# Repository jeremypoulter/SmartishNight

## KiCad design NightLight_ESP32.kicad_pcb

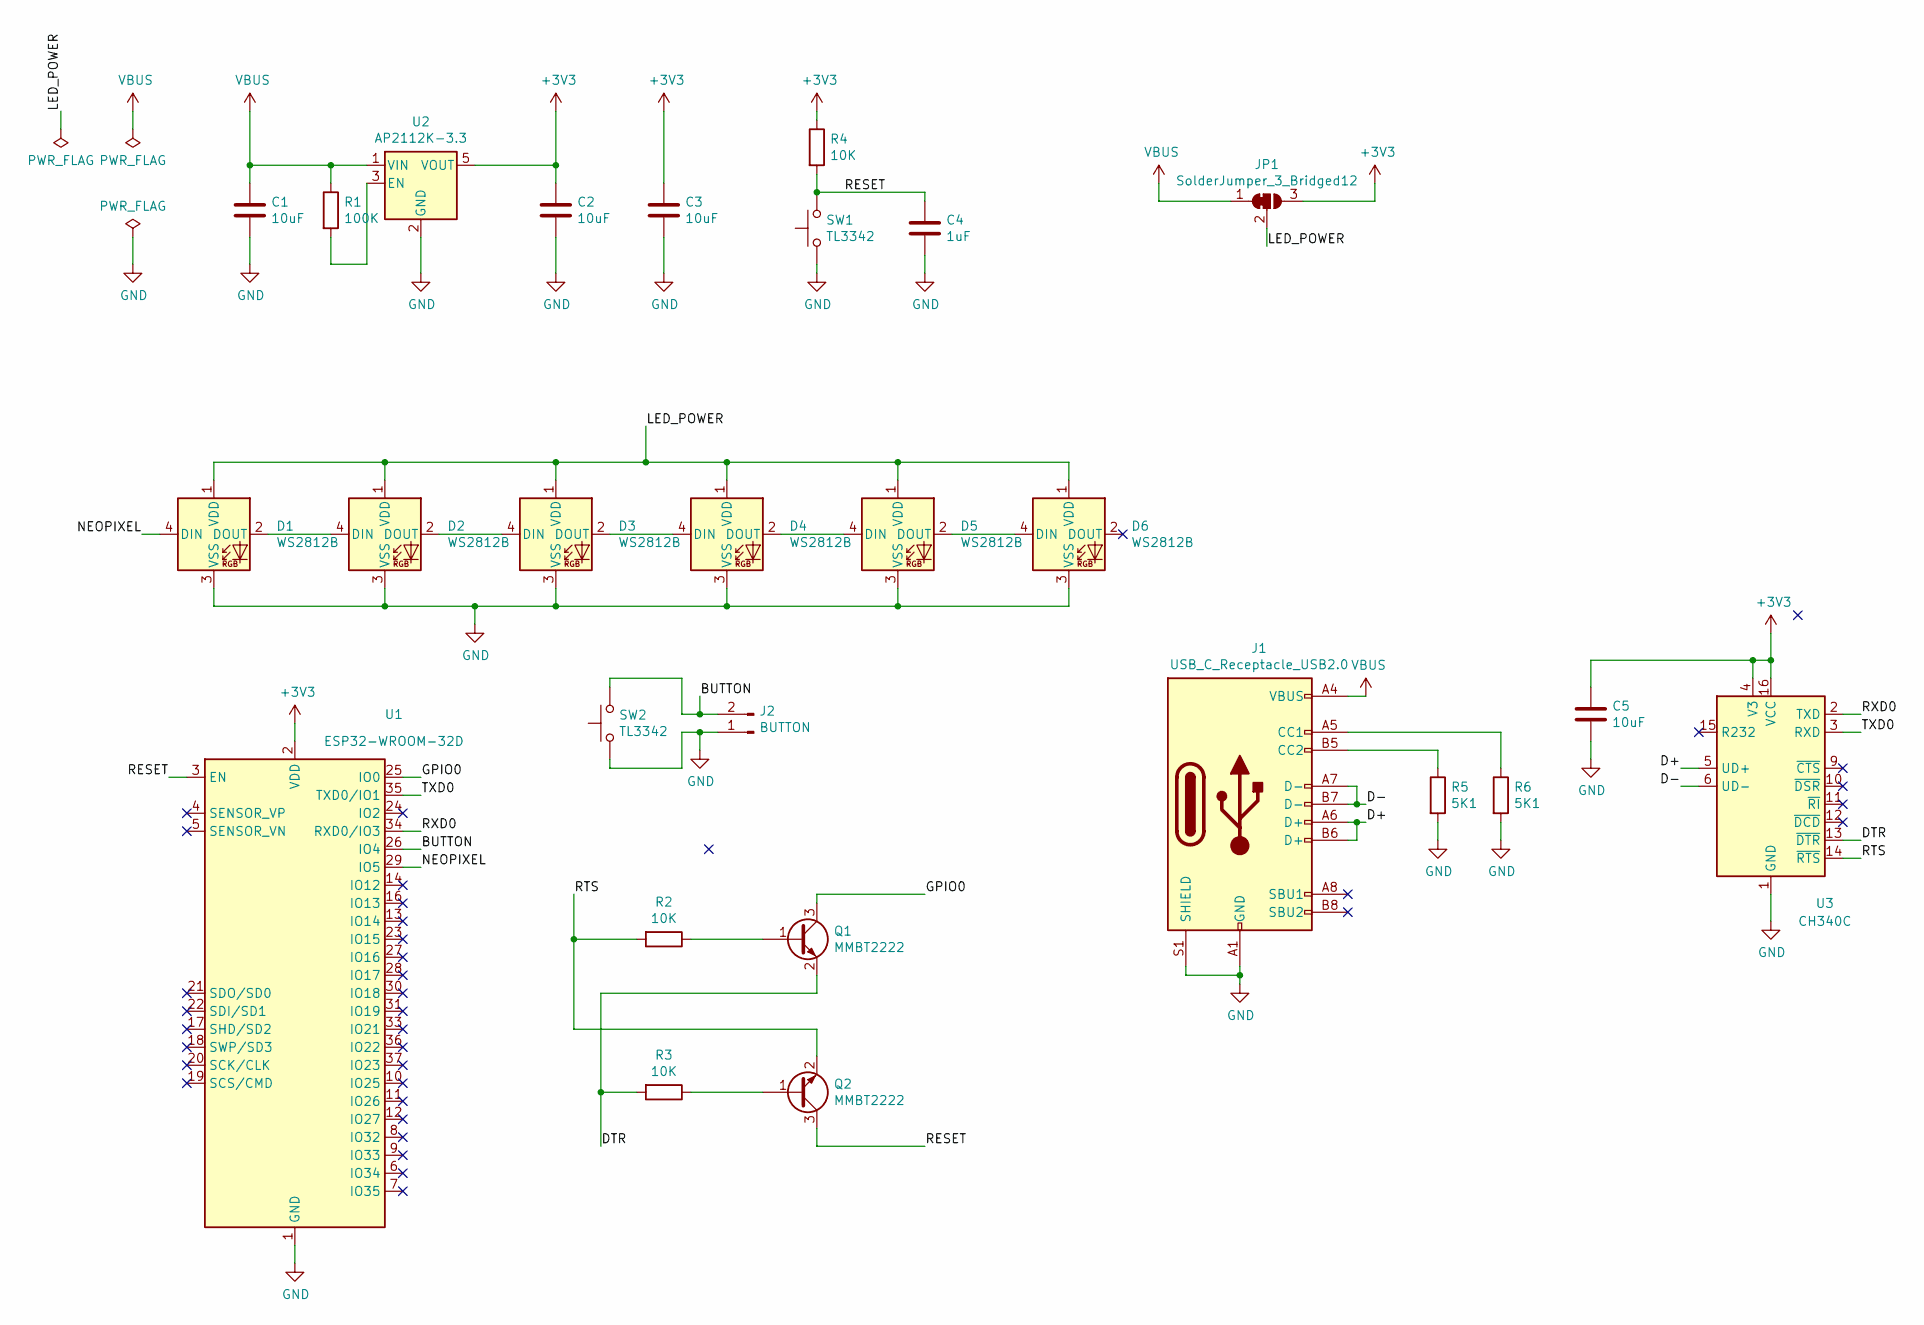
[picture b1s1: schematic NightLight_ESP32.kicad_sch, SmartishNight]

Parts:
C1, C2, C3, C5: 10uF; C_0805_2012Metric; LCSC C15850
C4: 1uF; C_0805_2012Metric; LCSC C28323
D1: WS2812B; LED_WS2812B_PLCC4_5.0x5.0mm_P3.2mm; LCSC C114586
D2, D3, D4, D5, D6: WS2812B; LED_WS2812B_PLCC4_5.0x5.0mm_P3.2mm; JLCPCB_CORRECTION 0;0;180
J1: USB_C_Receptacle_USB2.0; USB_C_Receptacle_HRO_TYPE-C-31-M-12; LCSC C165948
J2: BUTTON; PinHeader_1x02_P2.54mm_Vertical
JP1: SolderJumper_3_Bridged12; SolderJumper-3_P1.3mm_Bridged12_RoundedPad1.0x1.5mm
Q1, Q2: MMBT2222; SOT-23
R1: 100K; R_0805_2012Metric; LCSC C17407
R2, R3, R4: 10K; R_0805_2012Metric; LCSC C17414
R5, R6: 5K1; R_0805_2012Metric; LCSC C27834
SW1, SW2: TL3342; SW_SPST_TL3342; LCSC C318884
U1: ESP32-WROOM-32D; ESP32-WROOM-32; LCSC C473012
U2: AP2112K-3.3; SOT-23-5; LCSC C51118
U3: CH340C; SOIC-16_3.9x9.9mm_P1.27mm; LCSC C84681

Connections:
+3V3: C2.1, C3.1, C5.1, JP1.3 (B), R4.1, U1.2 (VDD), U2.5 (VOUT), U3.4 (V3), U3.16 (VCC)
/BUTTON: J2.2, SW2.2, U1.26 (IO4)
/D+: J1.A6 (D+), J1.B6 (D+), U3.5 (UD+)
/D-: J1.A7 (D-), J1.B7 (D-), U3.6 (UD-)
/DTR: Q1.2 (E), R3.2, U3.13 (~DTR)
/GPIO0: Q1.3 (C), U1.25 (IO0)
/LED_POWER: D1.1 (VDD), D2.1 (VDD), D3.1 (VDD), D4.1 (VDD), D5.1 (VDD), D6.1 (VDD), JP1.2 (C)
/NEOPIXEL: D1.4 (DIN), U1.29 (IO5)
/RESET: C4.2, Q2.3 (C), R4.2, SW1.2, U1.3 (EN)
/RTS: Q2.2 (E), R2.2, U3.14 (~RTS)
/RXD0: U1.34 (RXD0/IO3), U3.2 (TXD)
/TXD0: U1.35 (TXD0/IO1), U3.3 (RXD)
GND: C1.2, C2.2, C3.2, C4.1, C5.2, D1.3 (VSS), D2.3 (VSS), D3.3 (VSS), D4.3 (VSS), D5.3 (VSS), D6.3 (VSS), J1.A1 (GND), J1.A12 (GND), J1.B1 (GND), J1.B12 (GND), J1.S1 (SHIELD), J2.1, R5.2, R6.2, SW1.1, SW2.1, U1.1 (GND), U1.15 (GND), U1.38 (GND), U1.39 (GND), U2.2 (GND), U3.1 (GND)
unnamed: D1.2 (DOUT), D2.4 (DIN)
unnamed: D2.2 (DOUT), D3.4 (DIN)
unnamed: D3.2 (DOUT), D4.4 (DIN)
unnamed: D4.2 (DOUT), D5.4 (DIN)
unnamed: D5.2 (DOUT), D6.4 (DIN)
unnamed: J1.A5 (CC1), R6.1
unnamed: J1.B5 (CC2), R5.1
unnamed: Q1.1 (B), R2.1
unnamed: Q2.1 (B), R3.1
unnamed: R1.2, U2.3 (EN)
VBUS: C1.1, J1.A4 (VBUS), J1.A9 (VBUS), J1.B4 (VBUS), J1.B9 (VBUS), JP1.1 (A), R1.1, U2.1 (VIN)

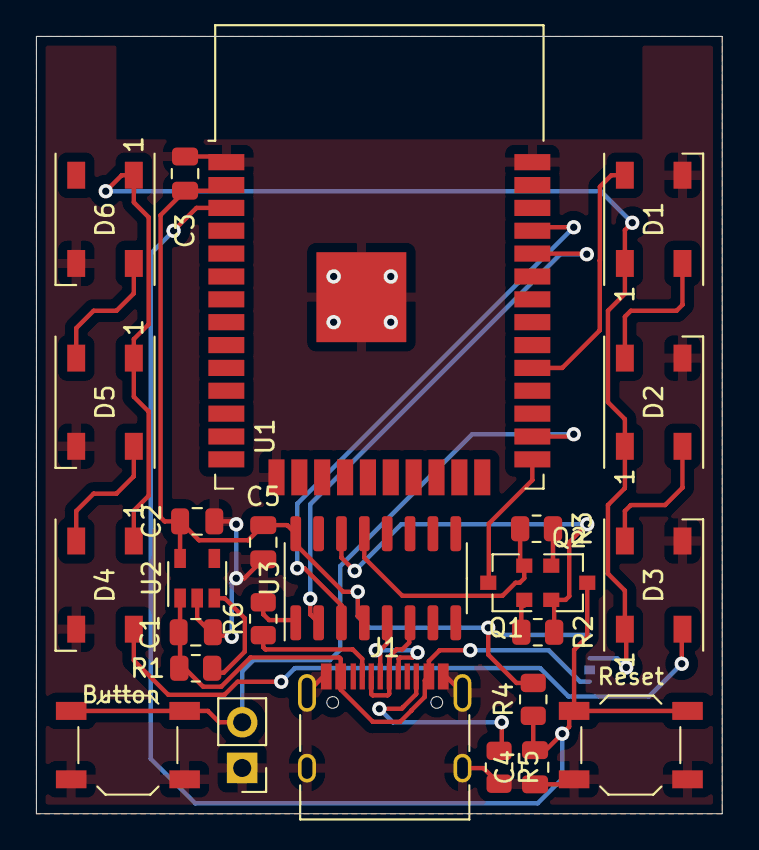
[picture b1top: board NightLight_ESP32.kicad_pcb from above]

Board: 2 copper layers, 38.1 x 43.2 mm, 27 parts (1 on the bottom side), 24 nets.

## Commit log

2020-11-03 Initial version
2020-11-03 Testing workflows for KiCAD
2020-11-03 Fixed spacing
2020-11-03 Updated sheet info
2020-11-03 Fix workflows
2020-11-03 Test commit
2020-11-03 Fixed name
2020-11-03 Fixed unconnected fills
2020-11-03 Tidy up of the silk screen
2020-11-03 Removed, not needed
2020-11-03 Adding fabrications job
2020-11-03 Renamed
2020-11-03 Trigger action
2020-11-03 Fixed unconnected GND area
2020-12-30 Fixed issues with serial lines not being connected correctly
2021-02-11 Updated LEDs power to be configurable from 5V or 3.3V
    Should be ok with a small circuot like this but close to the limits
2021-02-11 Fixed unconneced gnounds and a few other bits of tidy up
2021-02-11 Updated kicad-exports and generate JLCPCB BOM and position files
2021-02-11 Adding the workflow to the list of paths that will trigger the workflow
2021-02-11 Fix for action error
2021-02-11 Another attempt to run action on change to workflow
2021-02-11 Corrected kicad-exports version number
2021-02-11 The kicad-exports does not include the JLCPCB files, so adding locally
2021-02-11 Include JLCPCB files in workflow
2021-04-14 Changed to KiKit to generate the fabrication files
    including JLCPCB part numbers and position fixes
2021-04-28 Updated to USB C and CH340
2021-05-02 Added part corrections
2021-06-21 Fix issue with USB C CC1/CC2 needing two resistors and the wrong schematic symbol for the MMBT2222, leading to the wrong pinout
2021-07-30 Tall version of PCB
2021-07-31 A few tweeks
2021-07-31 Added generation of manufacturing files for tall version
2021-11-04 Added job to generate a release from the main branch
2021-11-04 Tweak to upload the assets
2021-11-04 Generate the docs for the tall version
2021-11-04 Fixed typo and removed rename of gerbers, will rename for the release
2021-11-04 Tidy up releases
2021-11-04 Now relase is based on tag so not a pre-release
2021-11-04 Fix artifact upload
2021-11-04 Fixed extensions on manufacturing files
2021-11-04 Set the as pre-release is the version contains -rc
2021-11-04 Fixing the renaming
2022-05-12 Corrected part for the USB C power signalling
2022-10-18 Updated to v6
2022-10-25 Updated to use KiBot directly to generate doc files
2022-10-25 Corrected the extensions for KiCAD 6
2022-10-25 Fix some DRC errors
2022-10-25 Corrected 3D models
